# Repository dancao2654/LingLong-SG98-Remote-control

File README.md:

# LingLong SG98 Firmware Workspace
Controller and handheld-remote firmware for the LingLong SG98 grinder platform,
covering both the main SG98 controller board and the standalone ESP32-S3 remote.

#### Developer documentation

For a full project walkthrough, architecture guide, workflow explanation, and motor protocol notes, start with:

- `Developer-Guide.md`
- `Documentation/IO-Reference.md`
- `Documentation/New-Motor-Backend-Guide.md`
- `Documentation/New-Motor-Backend-Implementation-Template.md`

#### TSE-B-D-100-KFM commissioning

**Partially hardware-tested replacement candidate 2026.11.03.1:** paired Controller/Waveshare1.75 builds
prepare explicit Start without PC, manual speed up to2000rpm and existing GBW/timed
purge controls. Both paired devices were flashed and supervised tests passed;
full acceptance remains pending. See the [hardware checkpoint](Documentation/TSE-KFM-Pruefstand-20261103.md).
See [scope, limitations and acceptance work](Documentation/TSE-KFM-Ersatzsteuerung-20261103-DE.md).

Earlier hardware-tested local candidate: **2026.10.28.6**. A real supervised shot at
800/300 rpm reached18.0g for an18g target and stopped without errors. Earlier
manual, purge, remote-loss and scale-loss tests retain their version labels.
This remains a bounded commissioning build: explicit USB arm per run,30-second
arm/run windows and800rpm maximum. It is not a standalone production release.
Factory input mapping and persistent PA24 are preserved by the candidate;
uncalibrated torque-based purge/learning remains excluded for KFM.

- [Historical results and settings for 2026.10.28.6 (German)](Documentation/TSE-KFM-Stand-20261028-DE.md)
- [Historical functional check plan](Documentation/TSE-KFM-Funktionspruefung-DE.md)
- [Earlier commissioning implementation](Documentation/TSE-KFM-Commissioning.md)
- Offline regression: `python3 tools/run_kfm_checks.py`
- Offline log report: `python3 tools/kfm_session_report.py SESSION_DIRECTORY --output NEW_REPORT_DIRECTORY`

#### Firmware targets

This repo contains two different ESP32-S3 firmware projects:

- repo root `.` = the SG98 controller box firmware
- `sg98-remote/` = the standalone SG98 hand-remote firmware project

For PlatformIO in the repo root `Project Tasks`:

- `adafruit_feather_esp32s3` = controller box on Adafruit hardware
- `waveshare_esp32_s3_rs485_can` = controller box on Waveshare hardware
- `controller-lilygo-t4-s3-h678` = controller firmware on LILYGO T4-S3 H678 with external RS-485 transceiver
- `remote-crowpanel-128` = CrowPanel 1.28 handheld remote
- `remote-crowpanel-21` = CrowPanel 2.1 handheld remote
- `remote-waveshare-175` = Waveshare 1.75 handheld remote
- `remote-lilygo-t4-s3-h678` = LILYGO T4-S3 H678 2.41 AMOLED two-button handheld remote
- `remote-universal-s3` = compatibility alias for the auto-detect remote image

The remote code still lives as a separate project in `sg98-remote/`, but the
root `platformio.ini` now exposes the same shipped remote hardware variants so
you can build both controller and remote firmware from one PlatformIO task tree.

The current universal remote image auto-detects these boards at boot:

- Elecrow CrowPanel 1.28 rotary/touch remote
- Waveshare 1.75 AMOLED touch remote
- LILYGO T4-S3 H678 2.41 AMOLED touch/two-button remote

The supported remote boards now share:

- a common remote HAL for board detect, input, display, power, and debug
- on-screen battery status for the Waveshare `AXP2101` PMIC path
- idle light-sleep with wake by touch/button on supported boards

The custom PlatformIO targets now also expose one-shot aggregate builds:

- `Build Universal Controller Firmware`
- `Build Universal Remote Firmware`
- `Build Universal Firmware Set`

Those aggregate/default project builds now target only:

- `controller-universal-s3`
- `remote-universal-s3`

The board-specific environments remain available for forced hardware debugging,
but they are no longer part of the normal aggregate build flow.

The LilyGO controller target currently treats the board as a controller carrier:
RS-485 UART is on `GPIO2` TX and `GPIO4` RX, the start button is on `GPIO21`,
and the rotary encoder uses `GPIO47`/`GPIO48` plus button `GPIO38`.

#### Versioning and upgrades

Firmware releases use the root `VERSION` file as the public release train, for
example `2026.04.28`. PlatformIO stamps every controller and remote build with:

- release version
- controller/remote role
- PlatformIO environment
- git short SHA
- dirty build marker
- UTC build date/time

That same identity appears in the last menu entry, `About`, and in the USB-C
`api device` response. The older `BUILD_ID` in `src/definitions.h` is still only
for saved-settings schema resets and should not be changed for normal releases.

Updater bundles use the same version metadata. From `2026.04.28` forward,
devices report `supportsAppOnlyUpdate=true`; the desktop updater and future
online updater can flash only the application partition when the running device
is at least the bundle's `appOnlySince` version, role/environment matches the
bundle, and the new app fits the current app partition. Older firmware,
unreadable devices, incompatible layout, or recovery cases fall back to full
flash. A release can force full flash by building the bundle with
`SG98_UPDATE_DEFAULT_MODE=full` or by raising `SG98_APP_ONLY_SINCE`.
For recovery cases where the running firmware reports incorrect USB-C identity
metadata, run the matching updater with `--force`; that skips the identity probe
and full-flashes the embedded controller or remote image. Use `--list` first to
see connected USB serial ports, identify likely `ESP32-S3` hardware, and copy the
matching `--force --port ...` command.

If an upgrade fails on the original SG98 controller board: keep +24 V
disconnected, run `SG98-Updater --list`, choose the port that reports SG98
identity or `ESP32-S3`, then retry with the printed `--force --port ...` command.
If no `ESP32-S3` appears, hold `BOOT` / `BOOT0`, tap `EN` / `RESET`, and run
`--list` again.

The generic controller build uses `partitions/controller_8mb_ota.csv`, which
keeps two 3.5 MB app slots on 8 MB controller hardware. Moving an existing
controller from the older single-app layout to this layout requires one USB full
flash. After that, the device can report `supportsOtaUpdate=true` and future
online updates can use the inactive OTA app slot.

Do not flash `sg98-remote` onto the SG98 controller box.

If the box boots with serial or screen text such as `SG98 remote`, `Set target MAC`, `MANUAL`, or `ESP-NOW ch1`, the remote firmware is on the wrong device.

To recover the box, flash the controller environment from the repo root:

```bash
~/.platformio/penv/bin/platformio run -e adafruit_feather_esp32s3 -t upload
```

#### How to use
Aquire a PCB (order through JLCPCB with the provided files or buy a readymade one). and wire it up correctly.
Install Visual Studio code, install the PlatformIO extension. Clone this repo.

Make sure to (un)comment the proper drive type in definitions.
Uploading to ESP32 through USB-C. Make sure +24v is not present. If necessary short press EN while holding BOOT0 button for uploading.
If flash error in final install, plugging in the USB C shortly after pressing "Upload" will make it work.

#### BLE error console

The firmware now exposes a lightweight BLE error-history dump so you can keep `24V` connected and still inspect faults without USB-C. The board keeps a 1024-entry rolling log of motor and scale warning/error activity, then dumps it over BLE later instead of keeping a live BLE monitor session open during scale use.

Install the macOS Terminal client dependency:

```bash
python3 -m pip install --user -r tools/requirements-ble-console.txt
```

Use the Terminal client:

```bash
python3 tools/ble_console.py
```

It connects, downloads the buffered event history, prints it, and exits. If there is no history, it prints `no logged errors`.

If the log is very full, give the client more time:

```bash
python3 tools/ble_console.py --dump-timeout 30
```

To avoid disturbing the scale connection, BLE console advertising pauses while the board is actively in scale mode. The safe bench-verified setup is:

- let the board run normally with the scale
- return to idle
- run `python3 tools/ble_console.py` to fetch any recorded errors

The ring buffer stores the latest 1024 recorded events only. Fetching the dump does not clear the history; it is a rolling log.

#### USB-C web console

The firmware now also exposes a structured USB-C console API so a local browser page can render a real control UI instead of plain serial text.

The browser app lives in:

- `tools/web_console`

Run it locally:

```bash
python3 -m http.server 8080 -d tools/web_console
```

Then open in Chrome or Edge:

```text
http://localhost:8080
```

What it gives you:

- live status over USB-C
- quick start/stop and drive-selection controls
- set RPM / target weight controls
- Menu 1 to Menu 4 rendered as a browser UI, including the JMC baud submenu

Notes:

- This path uses Web Serial over USB-C, so use Chrome or Edge on desktop.
- Bluefy is still relevant for the BLE path, not the USB-C path.
- The browser UI talks to `src/diag_console.cpp` through `api ...` commands.

#### Onboard WiFi web console

The board now also hosts its own phone-friendly web UI over the ESP32-S3 WiFi radio.

How it works:

- the board always starts its own access point:
  - `SG98-XXXXXX`
- connect your phone to that WiFi
- open:
  - `http://192.168.4.1/`

What the onboard page gives you:

- live grinding screen graphics
- quick start/stop and drive controls
- full Menu 1 to Menu 4 browser control
- WiFi settings page to save home SSID/password

Home-network mode:

- the board keeps its own AP up
- you can also save home WiFi credentials in the web UI
- after that, the board will also join your LAN and show its home-network IP in the page

USB-C serial boot log now prints the AP details too:

```text
[wifi] ap_ssid=SG98-XXXXXX ap_ip=192.168.4.1
```

#### BOM
- ESP32 PCB board + 90 degree 2.54 pins
- 1.69" round corner SPI color display + 2.54 female header
- 19mm ultra short throw momentary button with 3-5V LED.
- M12 4 pin female connector
- KCD1 SPST switch
- 3D printed box, including 4xM3x5Wx4L heat inserts and 2x m3*8 countersunk screw and m3*6 non-countersunk screw.
- A knob for the rotary encoder to your choosing.

-

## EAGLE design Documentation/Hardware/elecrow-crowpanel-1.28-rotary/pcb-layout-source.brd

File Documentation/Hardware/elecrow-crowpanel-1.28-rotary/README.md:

# Elecrow CrowPanel 1.28 Rotary

Local vendor documentation snapshot for the Elecrow `CrowPanel 1.28inch-HMI
ESP32 Rotary Display 240x240 IPS Round Touch Knob Screen`.

## Board Docs

- [official-wiki.html](./official-wiki.html)
  Source: `https://www.elecrow.com/wiki/CrowPanel_1.28inch-HMI_ESP32_Rotary_Display.html`
- [official-github-readme.md](./official-github-readme.md)
  Source: `https://github.com/Elecrow-RD/CrowPanel-1.28inch-HMI-ESP32-Rotary-Display-240-240-IPS-Round-Touch-Knob-Screen`
- [official-example-readme.md](./official-example-readme.md)
  Source: `https://github.com/Elecrow-RD/CrowPanel-1.28inch-HMI-ESP32-Rotary-Display-240-240-IPS-Round-Touch-Knob-Screen/tree/master/example`
- [arduino-lesson1.html](./arduino-lesson1.html)
  Source: `https://www.elecrow.com/wiki/CrowPanel_1.28inch-HMI_ESP32_Rotary_Display_Arduino_lesson1.html`
- [esphome-course.html](./esphome-course.html)
  Source: `https://www.elecrow.com/wiki/CrowPanel_HMI_ESP32_Rotary_Display_ESPHome_course.html`
- [esp32-display-hmi-user-manual.pdf](./esp32-display-hmi-user-manual.pdf)
  Source: `https://www.elecrow.com/download/product/ESP32_Display/ESP32_Display_HMI_User_Manual.pdf`

## Hardware Design Files

- [schematic-and-pcb-overview.pdf](./schematic-and-pcb-overview.pdf)
  Source: vendor GitHub `Eagle_SCH&PCB/ESP32 Display-1.28-V1.0.pdf`
- [schematic-source.sch](./schematic-source.sch)
  Source: vendor GitHub `Eagle_SCH&PCB/ESP32 Display-1.28-V1.0.sch`
- [pcb-layout-source.brd](./pcb-layout-source.brd)
  Source: vendor GitHub `Eagle_SCH&PCB/ESP32 Display-1.28-V1.0.brd`
- [display-module-datasheet.pdf](./display-module-datasheet.pdf)
  Source: vendor GitHub `Datasheet/0128B014-G1I0112...pdf`

## Shared Chip Docs

- See [../common-esp32-s3/README.md](../common-esp32-s3/README.md) for the
  `ESP32-S3` datasheet and technical reference manual.

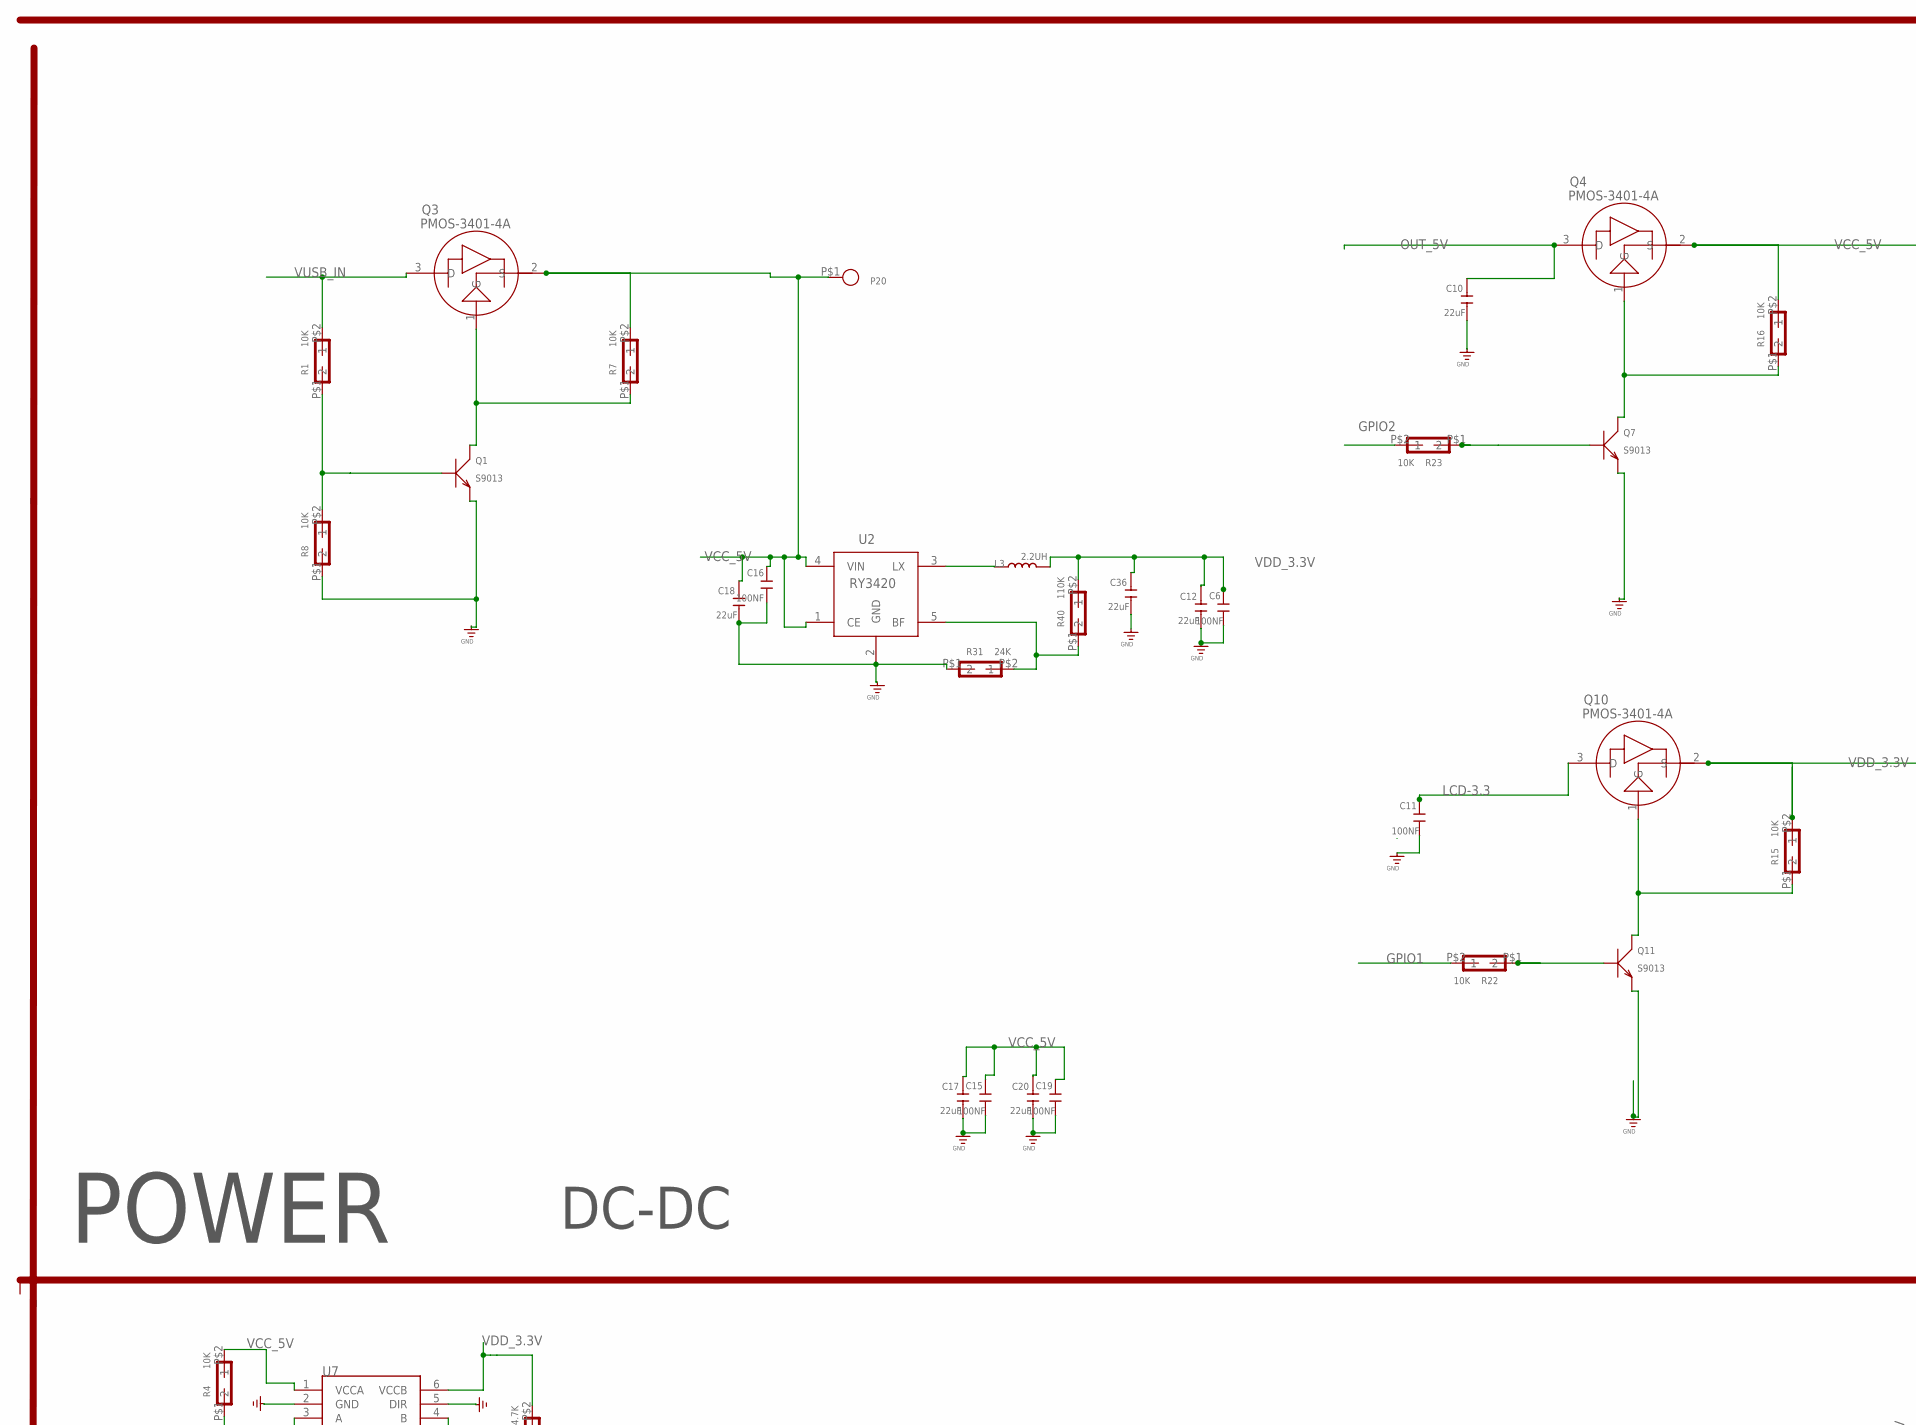
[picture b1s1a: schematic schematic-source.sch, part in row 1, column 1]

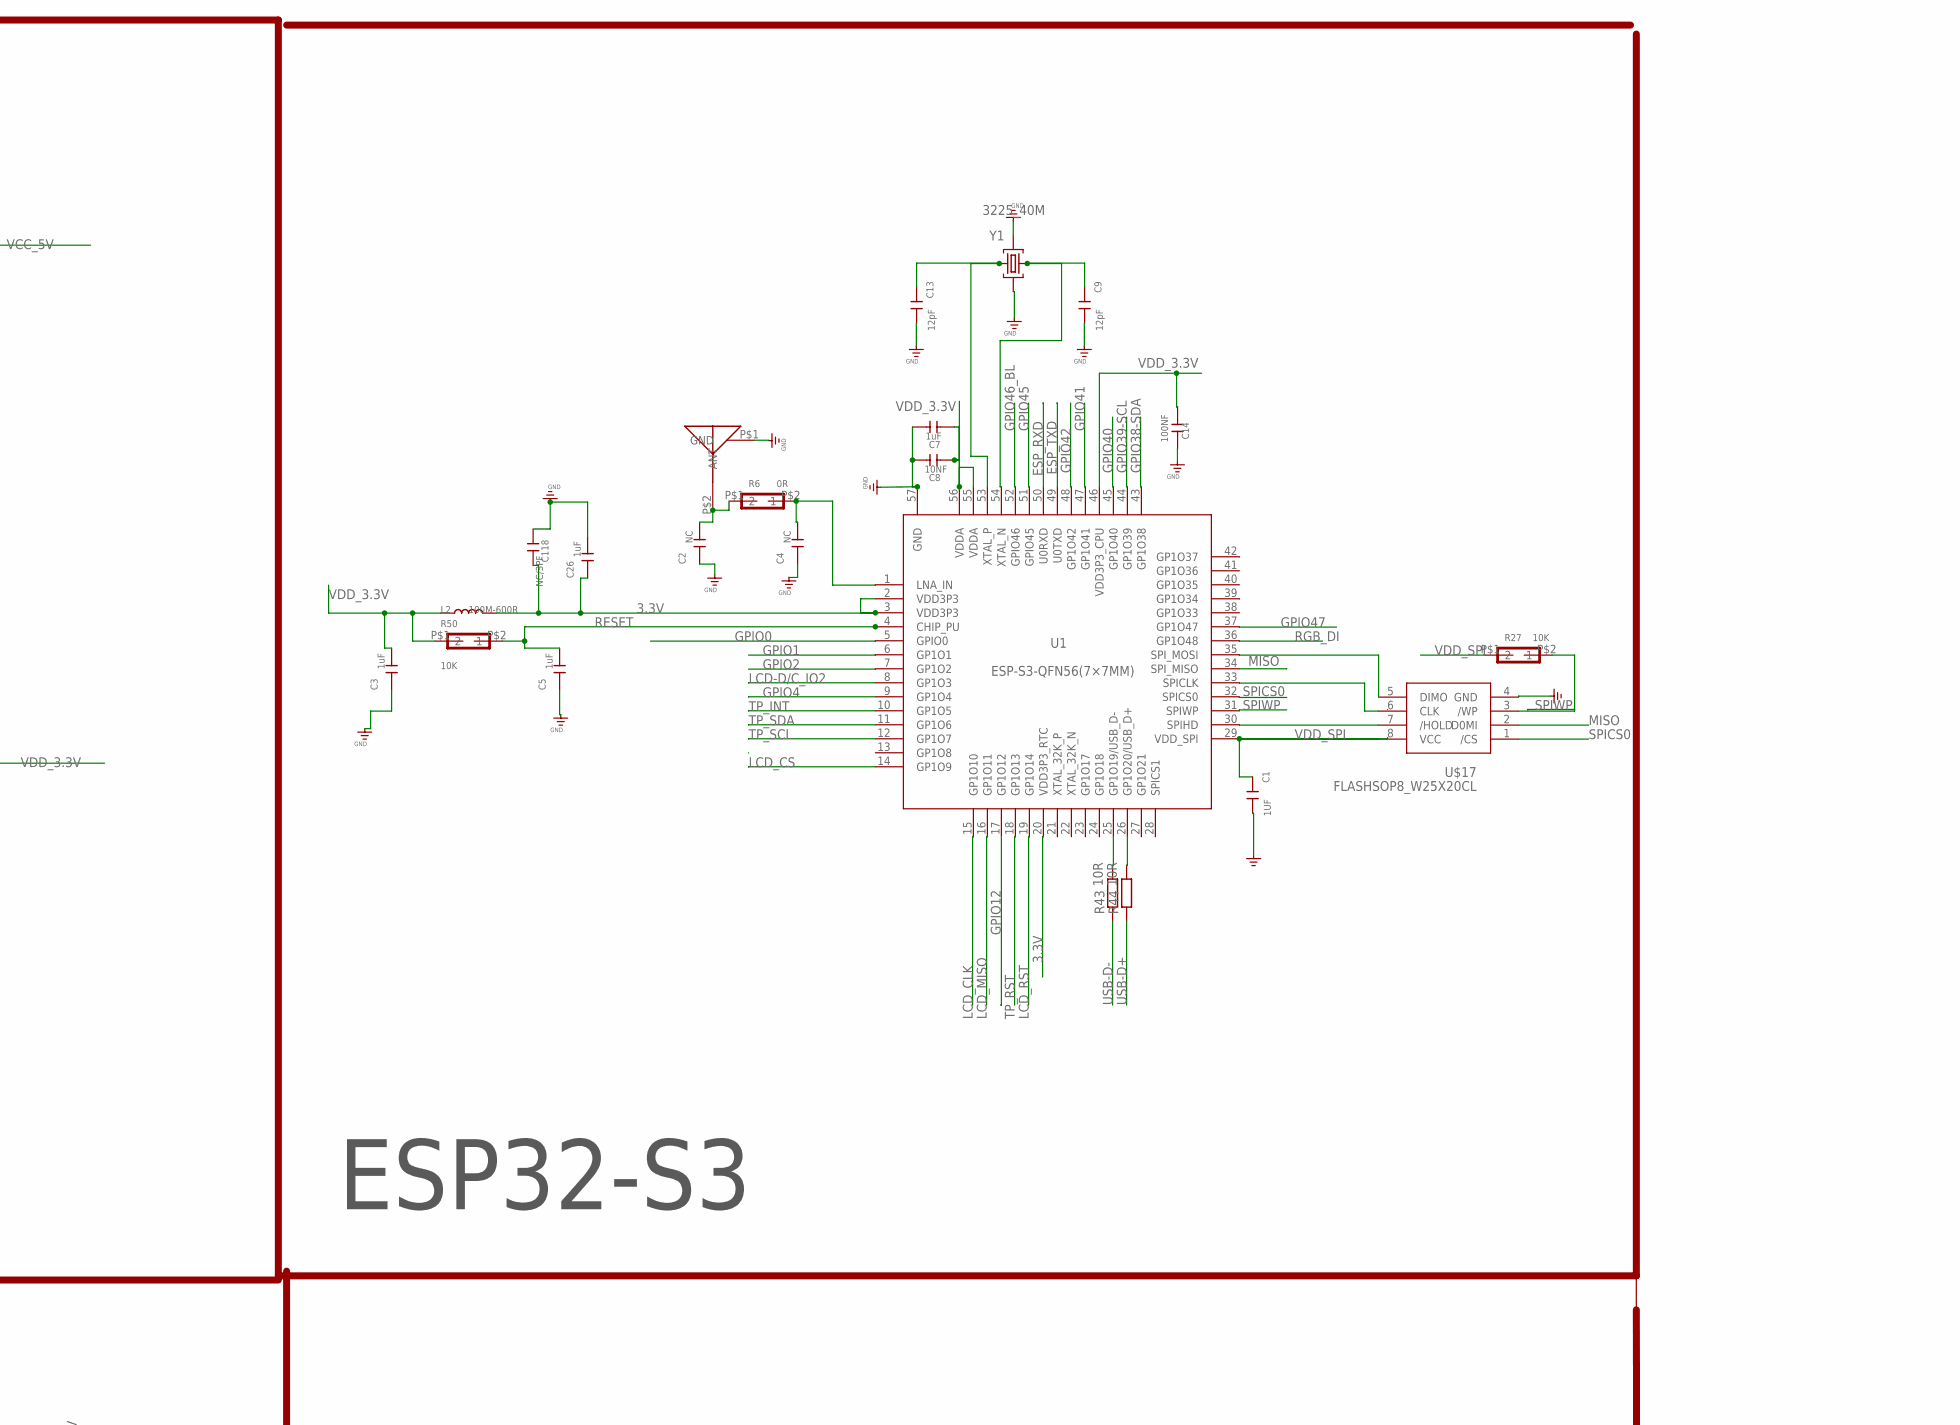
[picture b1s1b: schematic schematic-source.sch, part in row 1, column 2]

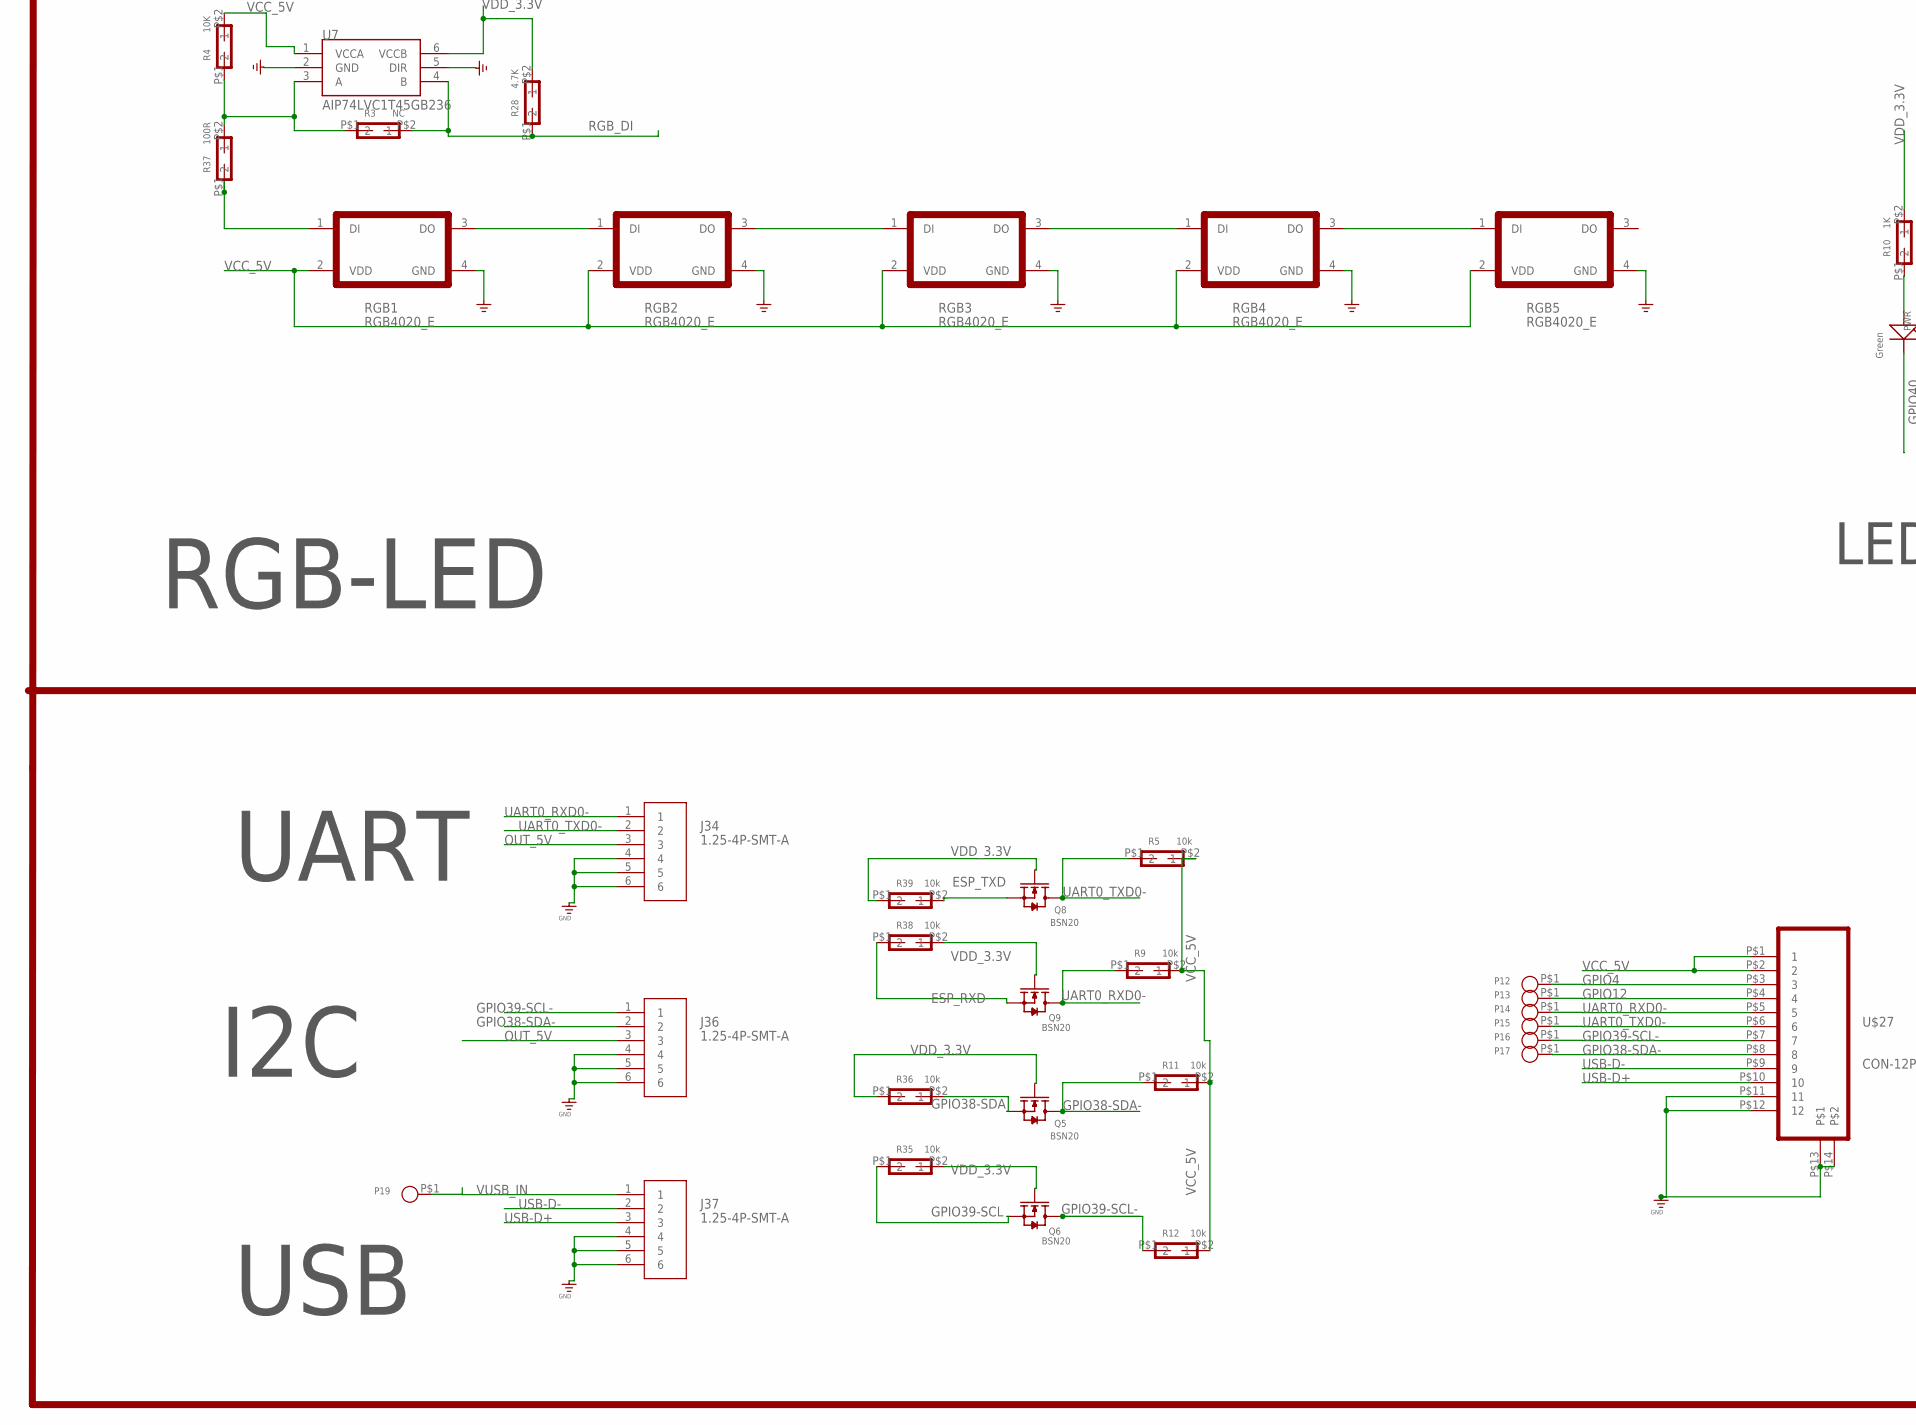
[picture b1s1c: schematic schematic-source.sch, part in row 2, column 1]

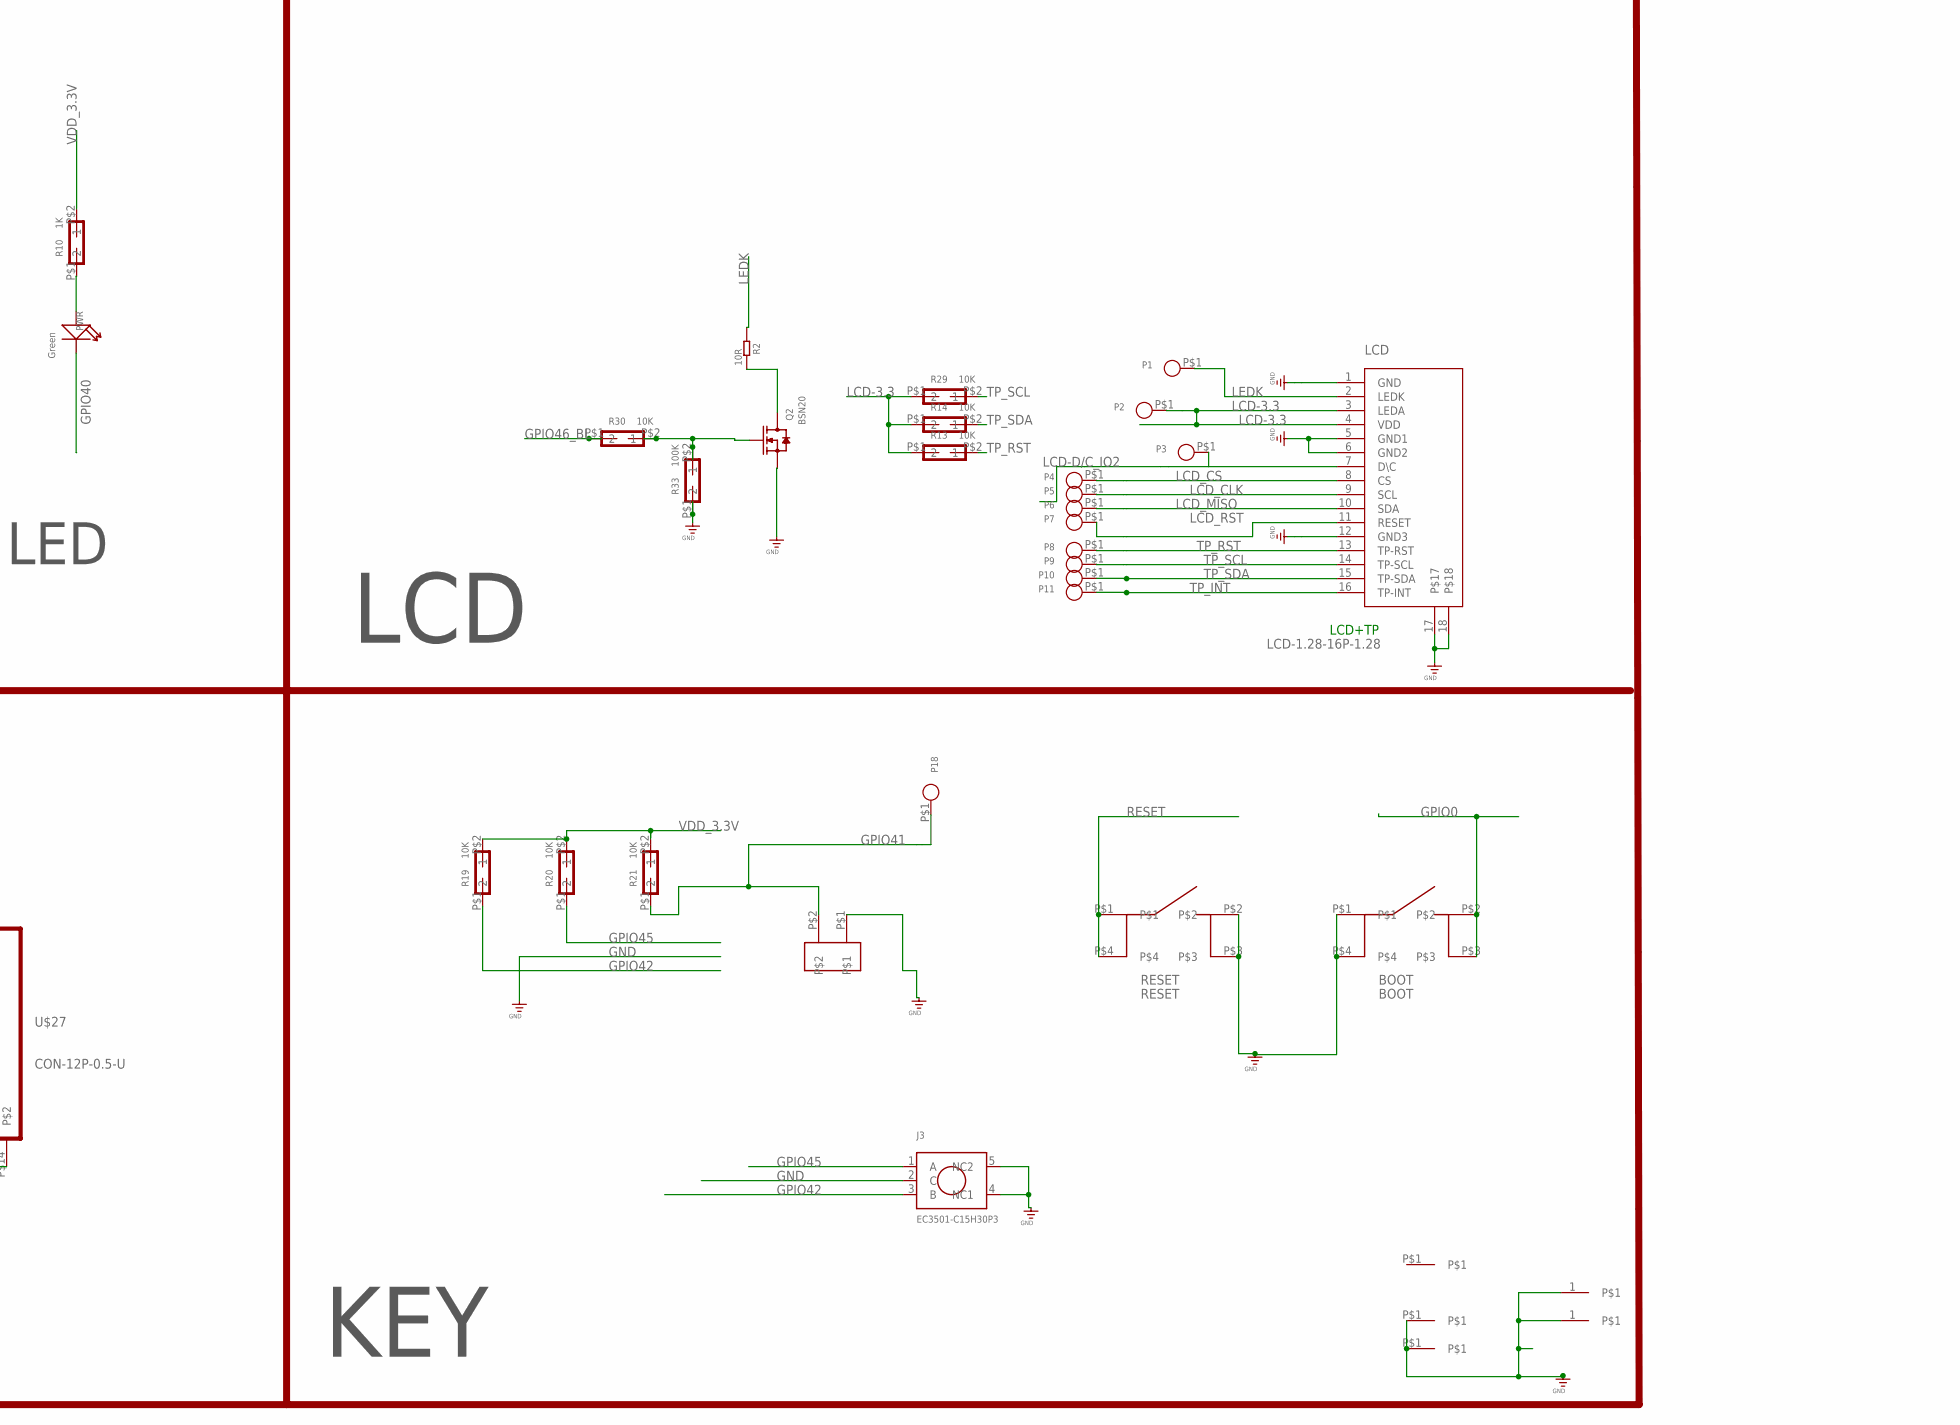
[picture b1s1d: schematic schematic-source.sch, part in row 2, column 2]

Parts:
ANT: BT_ANT
BOOT: BOOT; SW-4.5*4.5
C1: 1UF; 0402
C2, C4: NC; C0402
C3, C5, C26: 1uF; C0402
C6, C11, C15, C16, C19: 100NF; 0603
C7: 1uF; C0603
C8: 10NF; C0603
C9, C13: 12pF; 0402
C10, C12, C17, C18, C20, C36: 22uF; 0805
C14: 100NF; C0603
C118: NC/3PF; 0603
J3: EC3501-C15H30P3
J34, J36, J37: 1.25-4P-SMT-A; 1.25-4P立贴
K112: BUTTON_2P
L2: 100M-600R; L0603
L3: 2.2UH; L0420
LCD: LCD-1.28-16P-1.28; 0.5MM-16P
P1, P2, P3, P4, P5, P6, P7, P8, P9, P10, P11, P12, P13, P14, P15, P16, P17, P18, P19, P20: PADPAD-1.0MM; PAD-1.0MM
PWR: Green; LED-0603
Q1, Q7, Q11: S9013; SOT23@1
Q2, Q5, Q6, Q8, Q9: BSN20; SOT23
Q3, Q4, Q10: PMOS-3401-4A; SOT-23
R1, R4, R7, R8, R13, R14, R15, R16, R19, R20, R21, R22, R23, R27, R29, R30, R50: 10K; 0402
R2: 10R; R0603
R3: NC; 0402
R5, R9, R11, R12, R35, R36, R38, R39: 10k; 0402
R6: 0R; 0402
R10: 1K; 0402
R28: 4.7K; 0402
R31: 24K; 0402
R33: 100K; 0402
R37: 100R; 0402
R40: 110K; 0402
R43, R44: 10R; R0402
RESET: RESET; SW-4.5*4.5
RGB1, RGB2, RGB3, RGB4, RGB5: RGB4020_E; RGB4020
T1, T2: T2.5-A; T-2.5
U1: ESP-S3-QFN56(7×7MM)
U2: RY3420; SOT23-5
U7: AIP74LVC1T45GB236; SOT23-6L
U$17: FLASHSOP8_W25X20CL; FLASHSOP8_SOP8
U$27: CON-12P-0.5-U; CON-0.5-12P-U
U$28, U$30, U$31: T-2-1.1
Y1: 3225_40M; CRYSTAL-3.2-2.5

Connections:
3.3V: C26.1, C118.2, L2.2, U1.2 (VDD3P3), U1.3 (VDD3P3), U1.20 (VDD3P3_RTC)
ESP_RXD: Q9.2 (S), R38.P$1 (1), U1.50 (U0RXD)
ESP_TXD: Q8.2 (S), R39.P$2 (2), U1.49 (U0TXD)
GND: ANT.P$1 (GND), BOOT.P$1, BOOT.P$4, C1.2, C2.1, C3.1, C4.1, C5.1, C6.2, C7.2, C8.2, C9.2, C10.1, C11.2, C12.1, C13.2, C14.2, C15.2, C16.2, C17.1, C18.1, C19.2, C20.1, C26.2, C36.1, C118.1, J3.2 (C), J3.4 (NC1), J3.5 (NC2), J34.4, J34.5, J34.6, J36.4, J36.5, J36.6, J37.4, J37.5, J37.6, K112.P$1, LCD.1 (GND), LCD.5 (GND1), LCD.6 (GND2), LCD.12 (GND3), LCD.17, LCD.18, Q1.2 (E), Q2.2 (S), Q7.2 (E), Q11.2 (E), R8.P$1 (1), R31.P$1 (1), R33.P$1 (1), RESET.P$2, RESET.P$3, RGB1.4 (GND), RGB2.4 (GND), RGB3.4 (GND), RGB4.4 (GND), RGB5.4 (GND), T1.1, T2.1, U1.57 (GND), U2.2 (GND), U7.2 (GND), U7.5 (DIR), U$17.4 (GND), U$27.P$11 (11), U$27.P$12 (12), U$27.P$13, U$27.P$14, U$28.P$1, U$31.P$1, Y1.2 (GND), Y1.4 (GND)
GPIO0: BOOT.P$2, BOOT.P$3, U1.5 (GPIO0)
GPIO1: R22.P$2 (2), U1.6 (GP1O1)
GPIO2: R23.P$2 (2), U1.7 (GP1O2)
GPIO4: P12.P$1, U1.9 (GP1O4), U$27.P$3 (3)
GPIO12: P13.P$1, U1.17 (GP1O12), U$27.P$4 (4)
GPIO34: U1.39 (GP1O34)
GPIO37: U1.42 (GP1O37)
GPIO38-SDA: Q5.2 (S), R36.P$2 (2), U1.43 (GP1O38)
GPIO38-SDA-: J36.2, P17.P$1, Q5.3 (D), R11.P$1 (1), U$27.P$8 (8)
GPIO39-SCL: Q6.2 (S), R35.P$1 (1), U1.44 (GP1O39)
GPIO39-SCL-: J36.1, P16.P$1, Q6.3 (D), R12.P$1 (1), U$27.P$7 (7)
GPIO40: PWR.-, U1.45 (GP1O40)
GPIO41: K112.P$2, P18.P$1, R21.P$1 (1), U1.47 (GP1O41)
GPIO42: J3.3 (B), R19.P$1 (1), U1.48 (GP1O42)
GPIO45: J3.1 (A), R20.P$1 (1), U1.51 (GPIO45)
GPIO46_BL: R30.P$1 (1), U1.52 (GPIO46)
GPIO47: U1.37 (GP1O47)
LCD-3.3: C11.1, LCD.3 (LEDA), LCD.4 (VDD), P2.P$1, Q10.3 (D), R13.P$1 (1), R14.P$1 (1), R29.P$1 (1)
LCD-D/C_IO2: LCD.7 (D\C), P3.P$1, U1.8 (GP1O3)
LCD_CLK: LCD.9 (SCL), P5.P$1, U1.15 (GP1O10)
LCD_CS: LCD.8 (CS), P4.P$1, U1.14 (GP1O9)
LCD_MISO: LCD.10 (SDA), P6.P$1, U1.16 (GP1O11)
LCD_RST: LCD.11 (RESET), P7.P$1, U1.19 (GP1O14)
LEDK: LCD.2 (LEDK), P1.P$1, R2.2
MISO: U1.34 (SPI_MISO), U$17.2 (D0MI)
unnamed: Q4.1 (G), Q7.3 (C), R16.P$1 (1)
unnamed: RGB1.3 (DO), RGB2.1 (DI)
unnamed: L3.1, U2.3 (LX)
unnamed: RGB2.3 (DO), RGB3.1 (DI)
unnamed: PWR.+, R10.P$1 (1)
unnamed: Q1.3 (C), Q3.1 (G), R7.P$1 (1)
unnamed: ANT.P$2 (ANT), C2.2, R6.P$1 (1)
unnamed: RGB3.3 (DO), RGB4.1 (DI)
unnamed: Q1.1 (B), R1.P$1 (1), R8.P$2 (2)
unnamed: R43.2, U1.25 (GP1O19/USB_D-)
unnamed: Q2.3 (D), R2.1
unnamed: R31.P$2 (2), R40.P$1 (1), U2.5 (BF)
unnamed: Q2.1 (G), R30.P$2 (2), R33.P$2 (2)
unnamed: R44.2, U1.26 (GP1O20/USB_D+)
unnamed: R3.P$1 (1), R4.P$1 (1), R37.P$2 (2), U7.3 (A)
unnamed: R37.P$1 (1), RGB1.1 (DI)
unnamed: U1.35 (SPI_MOSI), U$17.5 (DIMO)
unnamed: U1.33 (SPICLK), U$17.6 (CLK)
unnamed: RGB4.3 (DO), RGB5.1 (DI)
unnamed: U1.30 (SPIHD), U$17.7 (/HOLD)
unnamed: Q10.1 (G), Q11.3 (C), R15.P$1 (1)
unnamed: Q11.1 (B), R22.P$1 (1)
unnamed: Q7.1 (B), R23.P$1 (1)
unnamed: C4.2, R6.P$2 (2), U1.1 (LNA_IN)
unnamed: C13.1, U1.53 (XTAL_P), Y1.3 (C2)
unnamed: C9.1, U1.54 (XTAL_N), Y1.1 (C1)
OUT_5V: C10.2, J34.3, J36.3, Q4.3 (D)
RESET: C5.2, R50.P$2 (2), RESET.P$1, RESET.P$4, U1.4 (CHIP_PU)
RGB_DI: R3.P$2 (2), R28.P$1 (1), U1.36 (GP1O48), U7.4 (B)
SPICS0: U1.32 (SPICS0), U$17.1 (/CS)
SPIWP: R27.P$2 (2), U1.31 (SPIWP), U$17.3 (/WP)
TP_INT: LCD.16 (TP-INT), P11.P$1, U1.10 (GP1O5)
TP_RST: LCD.13 (TP-RST), P8.P$1, R13.P$2 (2), U1.18 (GP1O13)
TP_SCL: LCD.14 (TP-SCL), P9.P$1, R29.P$2 (2), U1.12 (GP1O7)
TP_SDA: LCD.15 (TP-SDA), P10.P$1, R14.P$2 (2), U1.11 (GP1O6)
UART0_RXD0-: J34.1, P14.P$1, Q9.3 (D), R9.P$1 (1), U$27.P$5 (5)
UART0_TXD0-: J34.2, P15.P$1, Q8.3 (D), R5.P$1 (1), U$27.P$6 (6)
USB-D+: J37.3, R44.1, U$27.P$10 (10)
USB-D-: J37.2, R43.1, U$27.P$9 (9)
VCC_5V: C15.1, C16.1, C17.2, C18.2, C19.1, C20.2, P20.P$1, Q3.2 (S), Q4.2 (S), R4.P$2 (2), R5.P$2 (2), R7.P$2 (2), R9.P$2 (2), R11.P$2 (2), R12.P$2 (2), R16.P$2 (2), RGB1.2 (VDD), RGB2.2 (VDD), RGB3.2 (VDD), RGB4.2 (VDD), RGB5.2 (VDD), U2.1 (CE), U2.4 (VIN), U7.1 (VCCA), U$27.P$1 (1), U$27.P$2 (2)
VDD_3.3V: C3.2, C6.1, C7.1, C8.1, C12.2, C14.1, C36.2, L2.1, L3.2, Q5.1 (G), Q6.1 (G), Q8.1 (G), Q9.1 (G), Q10.2 (S), R10.P$2 (2), R15.P$2 (2), R19.P$2 (2), R20.P$2 (2), R21.P$2 (2), R28.P$2 (2), R35.P$2 (2), R36.P$1 (1), R38.P$2 (2), R39.P$1 (1), R40.P$2 (2), R50.P$1 (1), U1.46 (VDD3P3_CPU), U1.55 (VDDA), U1.56 (VDDA), U7.6 (VCCB)
VDD_SPI: C1.1, R27.P$1 (1), U1.29 (VDD_SPI), U$17.8 (VCC)
VUSB_IN: J37.1, P19.P$1, Q3.3 (D), R1.P$2 (2)

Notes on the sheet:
LED
RGB-LED
ESP32-S3
LCD+TP
UART
I2C
USB
LCD
DC-DC
POWER
KEY

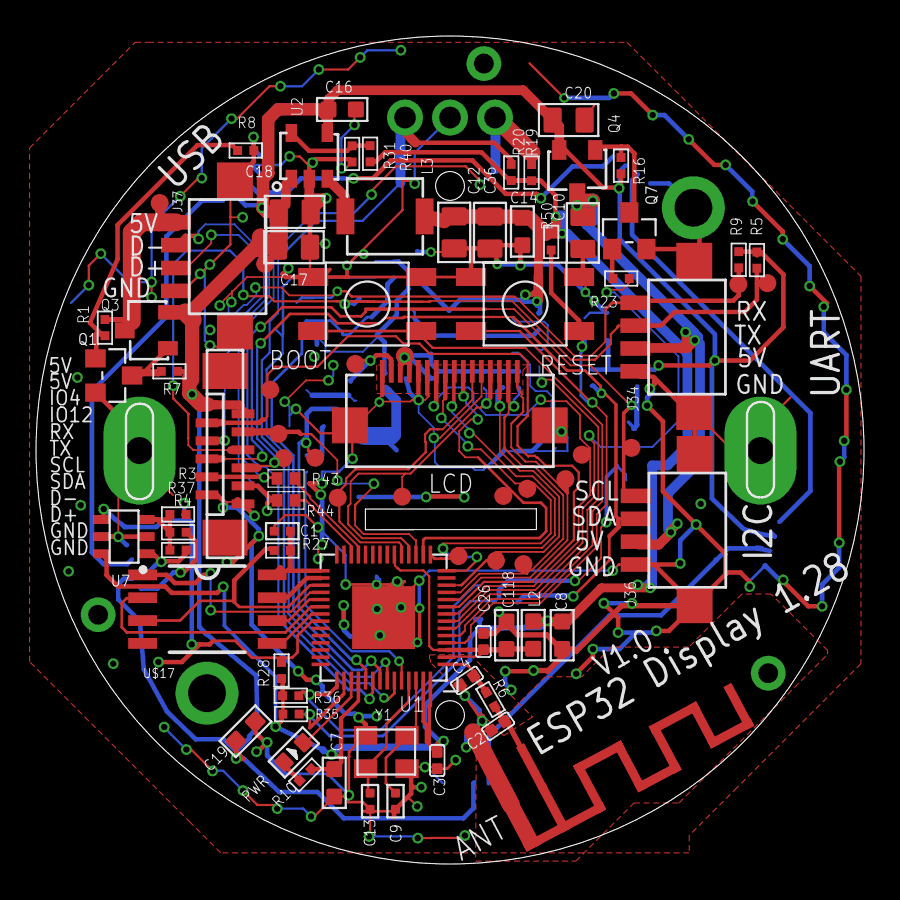
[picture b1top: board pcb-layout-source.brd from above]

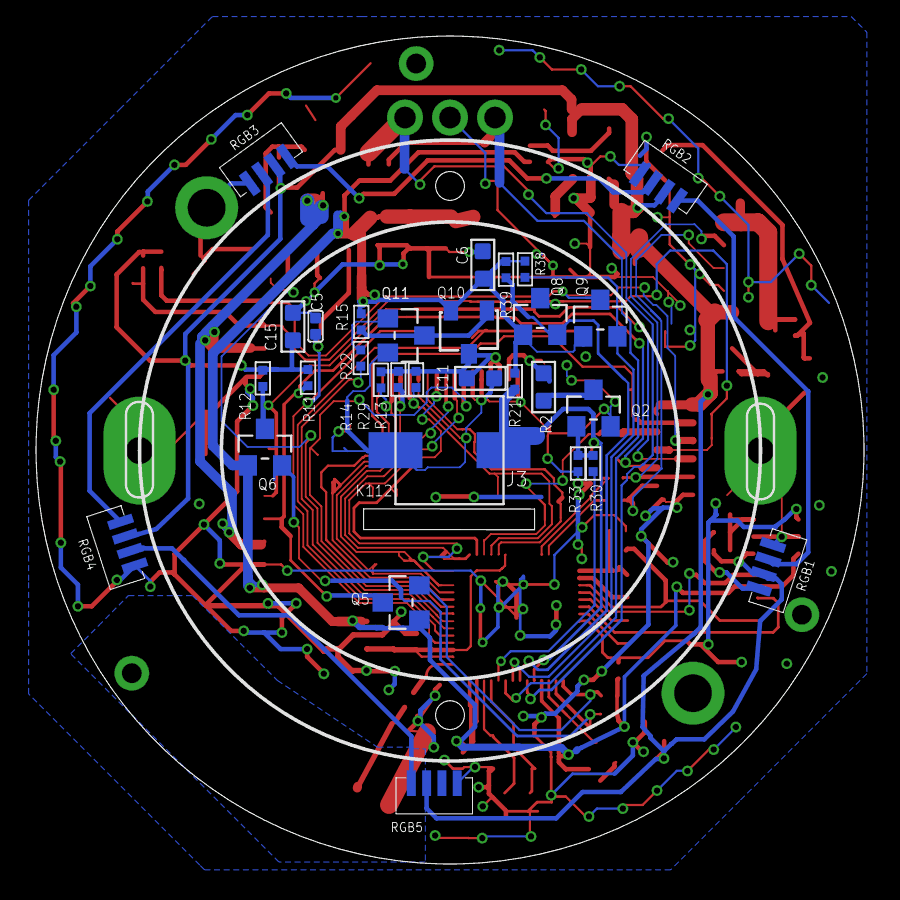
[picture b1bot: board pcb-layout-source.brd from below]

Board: 2 copper layers, 45.9 x 45.9 mm, 118 parts (33 on the bottom side), 69 nets.

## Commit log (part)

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2026-04-20 Improve JMC motor support and diagnostics
2026-04-20 Add web control consoles and WiFi onboarding
2026-04-20 add SG98 updater build infrastructure
2026-04-20 fix duplicate pdata helper definition
2026-04-20 add board esp-now mode and input fixes
2026-04-21 Add standalone SG98 remote firmware workspace
2026-04-21 Add CrowPanel 2.1 remote board support
2026-04-21 Add Wi-Fi remote WebSocket transport
2026-04-21 Improve remote sleep, telemetry, and controller ingress handling
2026-04-21 Add Waveshare headless target and reorganize motor backends
2026-04-22 Improve remote UX and add ESP-NOW discovery tooling
2026-04-22 Expand remote diagnostics and refine Waveshare support
2026-04-22 Add updater bundles and MD5 checksums
2026-04-22 Refresh SG98 bundles and workspace updates
2026-04-22 Add one-shot updater bundle task
2026-04-22 Refresh updater bundle archives and MD5 files
2026-04-22 Add cross-platform updater bundling tasks
2026-04-23 Migrate unified firmware to pioarduino
2026-04-23 Fix full-flash updater bundling for unified firmware
2026-04-23 Refine unified controller and remote firmware
2026-04-23 Polish controller calibration and RPM display
2026-04-23 Unify remote wake support and rework motor backends
2026-04-24 Reduce accidental motion returns to RUN
2026-04-24 Add motor backend onboarding guide PDF
2026-04-24 Add detailed motor backend implementation docs
2026-04-24 Add KRS backend and improve controller UX
2026-04-24 Add generated updater bundles
2026-04-25 Add headless remote safety deadman
2026-04-25 Regenerate updater bundles
2026-04-25 Update remote battery UI and responsiveness
2026-04-26 Add remote pressure profiler and orientation updates
2026-04-26 Update remote profiler BLE and dock UI
2026-04-27 Release latest SG98 firmware and bundles
    Includes the latest controller and remote firmware work, refreshed desktop updater bundles, connection matrix report, pressure wiring updates, and remote case assets.
    Notify: @isPointless @duerlis
2026-04-27 Harden ESP-NOW recovery and Wi-Fi bridge
    Default controllers to ESP-NOW-first operation while treating Wi-Fi enabled as WEB+ESP so the remote link stays available.
    Reject Wi-Fi-only and radio-off on headless controllers, open WEB+ESP recovery when ESP-NOW traffic disappears, and keep full-size standalone OFF available.
    Refresh the live connection matrix report and regenerate controller/remote updater bundles.
2026-04-27 Update remote networking and firmware bundles
2026-04-27 Polish wireless menu and sync environment packets
2026-04-28 Prepare OTA-capable release firmware
2026-04-28 Publish OTA release artifacts
2026-04-28 Wire public OTA manifest URLs
2026-04-28 Document release flow and clean build metadata
2026-04-28 Refresh SG98 OTA release artifacts
2026-05-01 Improve SG98 controller and remote connectivity UX
2026-05-01 Refresh SG98 release artifacts
2026-05-01 Harden remote WiFi STA connection
2026-05-01 Refresh remote OTA WiFi fix artifact
2026-05-01 Add OTA firmware cache buster
2026-05-01 Refresh remote OTA cache-busted artifact
2026-05-01 Separate OTA staging from updater bundles
2026-05-01 Refresh full updater bundles
2026-05-01 Add burr gap gauge support and updater recovery
2026-05-01 Refresh public updater bundles
2026-05-01 Block skipped serial ports in updater
2026-05-01 Refresh updater bundles for port picker guard
2026-05-01 Allow debug console as force recovery port
2026-05-01 Probe debug console recovery ports
2026-05-01 Refresh updater bundles for debug console recovery
2026-05-06 Add burr gap gauge support
    Generalize gauge GPIO mapping, display burr gap on controller and remote, add controller-owned Gauge Set persistence, and handle gauge dropout by saving the last displayed gap as the base without liv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
2026-05-07 Bring up LilyGO remote and harden OTA recovery
2026-05-07 Gate headless controller OTA apply on ready marker
2026-05-07 Add remote-driven controller OTA recovery flow
2026-05-07 Regenerate SG98 updater and OTA bundles
2026-05-08 Enable remote self OTA from About
2026-05-08 Stage remote OTA for About self-update
2026-05-15 Update SG98 firmware and OTA assets
2026-05-15 Stage controller OTA assets
2026-05-15 Use sweep pulses for purge vibration
2026-05-15 Stage sweep purge controller OTA assets
2026-05-16 Add SEW MOVILINK drive backend
2026-05-16 Refresh OTA artifacts for SEW support
2026-06-18 Add EX_I2C RS485 fallback diagnostics
2026-06-18 Retry AUTO motor detection before start
2026-06-18 Refresh controller OTA artifacts
